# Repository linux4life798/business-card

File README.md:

# PCB Business Card with NFC

A thin, wallet-size PCB business card combining printed contact details, a vCard
QR code, custom copper and silkscreen artwork, and passive NFC.

*KiCad 3D renders of the front and back, with gold on exposed copper.*

## Make it yours

You can personalize and export the card entirely through **KiCad 10**.
Python and GitHub Actions are optional conveniences.

1. Download or clone the whole project folder and open
   [business-card.kicad_pro](business-card.kicad_pro).
2. In the schematic, open **INFO1** properties and edit its `CONTACT_*` fields.
   Company, role, phone, email and website are optional. `CONTACT_WEB` is the
   printed address; `CONTACT_WEB_QR` is the QR's full URL, including `https://`.
3. Use **Update PCB from Schematic (F8)** with **Update footprint fields from
   symbols** enabled.
4. **Save, close and reopen the PCB Editor** to refresh KiCad 10's QR pattern.
   Check the text layout and scan the QR to confirm your details.
5. Run **Inspect → Design Rules Checker** and review its findings. Export Gerbers
   and drill files from **File → Fabrication Outputs** when ready to order.

<details>
<summary>Optional: automated exports</summary>

The [finalizer](copy-and-customize.py) creates a personalized project copy and export
bundle. It uses the saved INFO1 values; to override them only in the exported
copy, copy [contact.example.toml](contact.example.toml) to `contact.toml` and edit
it. Omitted keys keep the INFO1 value; `""` clears an optional field. For CI,
`CONTACT_*` environment variables override both TOML and INFO1, including empty values.

Use Python 3.11+ with KiCad 10's `kicad-cli` on your PATH and standard 3D model
libraries installed. No pip packages or virtual environment are needed:

```sh
python3 copy-and-customize.py
python3 copy-and-customize.py --config contact.personal.toml --output output/personal
```

On Windows, use `python` instead of `python3`. The **KiCad 10 Command Prompt**
provides access to `kicad-cli`.

The bundle contains a project-folder copy, Gerbers/drills and drill-map PDFs in
`fab/`, refreshed schematic SVG/PDF and front/back renders in `docs/`, and `drc.rpt`.
Local settings, contact files, caches and previous exports are excluded.
It defaults to `output/<timestamp>/` plus one ZIP, preserving source files and
existing exports. Review the report and previews before ordering; DRC findings
do not prevent export. The exported project remains editable through the same
INFO1 workflow; regenerate fabrication files after further edits.

For builds on GitHub, see the [private-repository action and starter workflow](automation/README.md).

</details>

## Explore the design

The NFC circuit uses an NXP NT3H2111W0FHKH (NTAG I2C Plus) and a printed antenna.
It is designed to illuminate an LED using energy from the reader's field,
with no onboard battery or microcontroller.

- [Schematic](business-card.kicad_sch) and [PCB layout](business-card.kicad_pcb).
- Project [symbols](business-card.kicad_sym), [footprints](business-card.pretty/)
  and [3D models](business-card.3dshapes/).
- [Artwork](artwork/) and its source SVGs.

INFO1 supplies the fields used by the
[contact-info footprint](business-card.pretty/Contact_Info_SilkScreen.kicad_mod)
for its text and native QR. If a footprint library update restores default
contact values, repeat F8 and the save/reopen step to reapply your details.

## Fabrication

Fabrication targets a two-layer, 0.6 mm FR-4 board with 1 oz copper, black solder
mask, and lead-free HASL.

Antenna tuning, NFC read range, and LED brightness require validation on
assembled hardware.

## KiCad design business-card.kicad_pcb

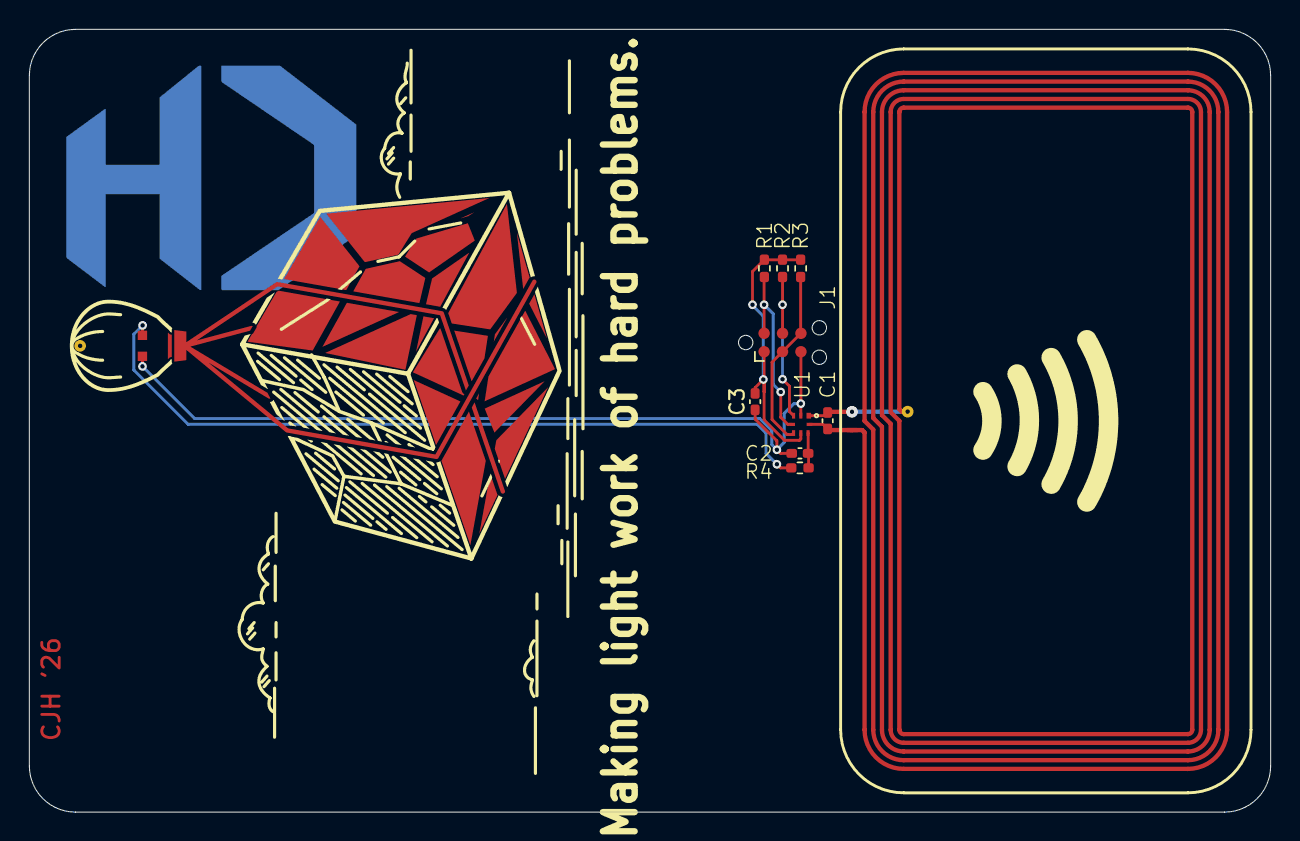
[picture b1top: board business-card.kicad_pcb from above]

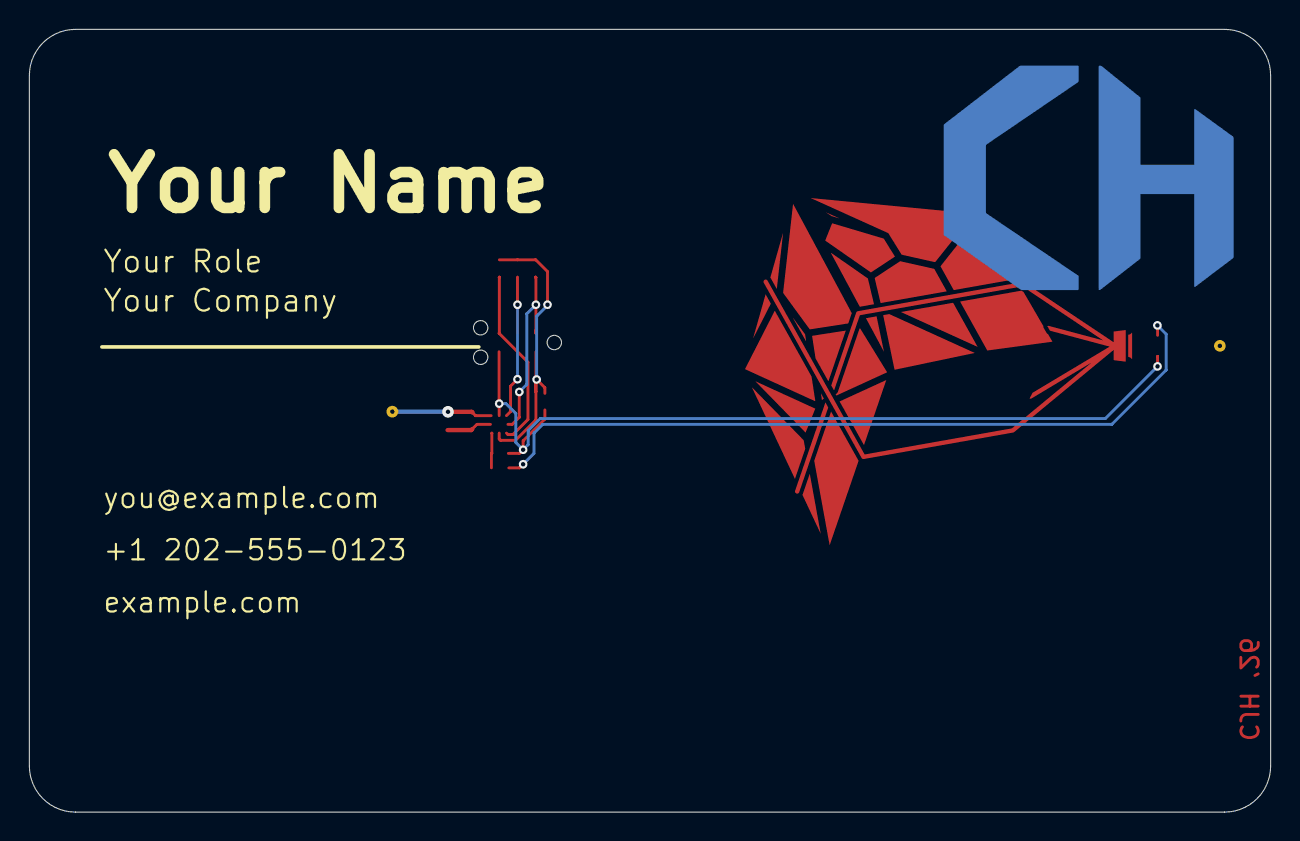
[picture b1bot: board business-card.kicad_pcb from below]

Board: 2 copper layers, 85.6 x 54.0 mm, 15 parts (2 on the bottom side), 9 nets.

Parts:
ART1: LanternLift_GiftWrap; LanternLift_GiftWrap_Copper_SilkScreen
C1: 5.1pF; C_0402_1005Metric_Pad0.74x0.62mm_HandSolder
C2, C3: 180nF; C_0402_1005Metric_Pad0.74x0.62mm_HandSolder
D1: A-SP192SS1C-C01-3C; Amicc_A-SP192SS1C-C01-3C_SideView
INFO1: Contact_Info; Contact_Info_SilkScreen
J1: TC2030; Tag-Connect_TC2030-IDC-NL_2x03_P1.27mm_Vertical
L1: Loboat_NFC_Antenna; Loboat_NFC_Antenna_48x25mm_5Turns
LOGO1: CH_Logo; CH_Logo_20mm_Copper
R1: 10k; R_0402_1005Metric_Pad0.72x0.64mm_HandSolder
R2, R3: 2.2k; R_0402_1005Metric_Pad0.72x0.64mm_HandSolder
R4: 330; R_0402_1005Metric_Pad0.72x0.64mm_HandSolder
SIGN1: CJH_Signature; CJH_Signature_Copper_Masked
U1: NT3H2111W0FHKH; NXP_SOT902-3_XQFN-8_1.6x1.6mm

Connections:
/LA: C1.1, L1.P$2, U1.1 (LA)
/LB: C1.2, L1.P$1, U1.8 (LB)
/SCL: J1.4, R2.2, U1.3 (SCL)
/SDA: J1.3, J1.6, R3.2, U1.5 (SDA)
/led: D1.1 (A), R4.2
/~FD: J1.2, R1.2, U1.4 (FD)
GND: C2.2, C3.2, D1.2 (K), J1.5, U1.2 (VSS)
VBUS: C2.1, R4.1, U1.7 (VOUT)
VCC: C3.1, J1.1, R1.1, R2.1, R3.1, U1.6 (VCC)

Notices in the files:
parts and their libraries:
Loann Boudin NFC antenna, 48x25 mm, 5 turns; Eagle conversion, CC BY-NC-SA 4.0
License: CC BY-NC-SA 4.0; https://creativecommons.org/licenses/by-nc-sa/4.0
